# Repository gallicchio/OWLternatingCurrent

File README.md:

# OWLternating Current

*By Jason Gallicchio, made with Claude. A cute, physics-y Halloween board set for a
six-year-old witch who wants to be an owl: owls, bats and a little witch on her broom
across a gold moon, in orange and purple light that fades but never blinks, with magnets
and coils doing things that look like magic.*

| The base board's LEDs fading on the bench | The bat caught under the owl's perch, then hovering |
|:---:|:---:|
|  |  |

*The rev A boards working on the bench, November 2026 (quick phone clips; click for the MP4).*

*Rendered from the design files (KiCad and Blender, `tools/render_3d.py`).*

**Status (2026-10-09):** designed, every net routed on all six boards, KiCad's DRC clean,
reviewed by five readers before the first order ([`DESIGN_REVIEW.md`](DESIGN_REVIEW.md),
[`docs/REVIEW_2026-10-09.md`](docs/REVIEW_2026-10-09.md)), the JLCPCB release written
(`mfg/release/`). Ordered from JLCPCB; the boards arrived on 2026-11-05, and their
bring-up is [`BRINGUP.md`](BRINGUP.md).

## What it does

| feature | what you see | the physics |
|---|---|---|
| **Light show** | violet stars, orange pumpkins that flicker like candles, purple will-o'-wisps, owls whose eyes open at dusk | 49 LEDs on two LP5036 drivers, every change a fade; dusk and dawn from a light sensor |
| **Wireless familiars** | put the owl token or the cat token on its perch and its eyes light; each perch lights only its own animal | resonant inductive power: each perch drives its coil at its token's frequency (owl 142 kHz, cat 303 kHz) and finds it by the rise in its own supply current, the power the token takes |
| **The pendulum bat** | a bat on a thread that never stops swinging, or circles the moon | three coils under the swing give it timed kicks; a 3-axis Hall sensor under the rest point times them |
| **The levitating bat** | the bat floats in the air under the owl's perch | a magnet in the printed owl holds the bat's magnet up; a 10 kHz loop on a Hall sensor and the perch's coil keeps it from falling or jumping up (Earnshaw's theorem says it cannot float on magnets alone) |
| **Theremin** | move a hand toward the gold moon and a note rises; toward the gold ghost and it gets louder | two relaxation oscillators whose capacitance includes your hand; a speaker a slide switch turns off |
| **The spell book** | the back of the base: the equations behind each trick | silkscreen |

## The boards

One 4-layer panel (JLCPCB, 1.6 mm, purple solder mask, ENIG), assembled by JLCPCB on both
sides, all but three connectors (the tree's two headers and the perch's socket, soldered at
home: 48 joints). The six boards snap apart and plug together: the tree stands in the
base's socket, the perch sits on the tree.

| board | from above | from below | in perspective |
|---|---|---|---|
| **Base** (190 x 130 mm): the electronics underneath, the scene on top |  |  |  |
| **Tree** (76 x 112 mm): the owls' eyes, stars, the second LED driver |  |  |  |
| **Perch**: the levitation coil, the Hall sensor in its middle |  |  |  |
| **Bat**: a receive coil round its magnet, LED eyes, no battery |  |  |  |
| **Owl token**: a coil, a tank capacitor, two LEDs |  |  |  |
| **Cat token** |  |  |  |

The panel as it comes from JLCPCB (245.2 x 223.2 mm), top and bottom:

## Making one

- [`ORDER_LIST.md`](ORDER_LIST.md): everything to buy (the boards, three connectors, a
  12 V adapter, two magnets, a little PLA, thread and a drop of glue) and what it costs
  (about $565 for five panels, two of them assembled).
- [`mfg/release/`](mfg/release/): the upload for JLCPCB, and `FABRICATION_NOTES.txt`,
  which walks down their order form field by field.
- [`print/README.md`](print/README.md): the owl, the bat's cap and four feet, on one plate,
  with one pause to drop in the magnets.
- [`firmware/README.md`](firmware/README.md): the RP2354A's firmware, flashed over USB-C.
- [`BRINGUP.md`](BRINGUP.md): the first power-up, step by step, with the bench scripts in
  [`bringup/`](bringup/) (the supply, scope and generator from Python, and a simulated
  bench to try every step on).

## Building it from source

Everything is generated from scripts: nothing on the boards is drawn by hand in KiCad.

```
python3 build.py              # every step, about 40 minutes
python3 build.py board        # from one step on
python3 build.py --only drc   # one step
```

The steps: the KiCad library, the project and its rules, the schematics, ERC, the
netlist's checks, the art, the boards (placement, planned copper, routing, pours), DRC,
the JLCPCB release, and the pictures on this page. It needs KiCad 10, Blender 4.2 or later
and Python 3. The outputs (`hardware/`, `mfg/release/`, `docs/images/`) are committed, so
nothing has to be built to look at the design or to order it.

## What's where

| path | what |
|---|---|
| [`DESIGN_REVIEW.md`](DESIGN_REVIEW.md) | the design, subsystem by subsystem, with its numbers, its checks and its open questions |
| [`BRINGUP.md`](BRINGUP.md), [`bringup/`](bringup/) | bringing the boards up at the bench, step by step, with the scripts and each day's results |
| [`bringup/REVB.md`](bringup/REVB.md) | everything rev B should change, and every question the bench has not yet answered |
| [`hardware/`](hardware/) | the KiCad project: schematics, the panel, the library, the checks' reports |
| [`gen/`](gen/) | the generators: parts, schematics, placement, art, coils, routing, the panel |
| [`mfg/`](mfg/) | the JLCPCB release and its checks |
| [`firmware/`](firmware/) | the firmware, with host tests against simulated physics |
| [`print/`](print/) | the 3D-printed parts (OpenSCAD, from the same numbers as the boards) |
| [`sim/physics/`](sim/physics/README.md) | magnetostatics and circuit simulations: wireless power, pendulum kicks, levitation |
| [`sim/antenna/`](sim/antenna/) | an openEMS study of character-shaped 2.4 GHz antennas, for a later revision |
| [`tools/`](tools/) | checks, renders, KiCad helpers |
| [`PLAN.md`](PLAN.md) | the ideas (41, with difficulty, cost and first-try odds), the choices, the schedule |
| [`CLAUDE_CODE_CHAT.md`](CLAUDE_CODE_CHAT.md) | the conversation that designed it, every prompt and response |
| [`research/`](research/) | the JLCPCB parts survey and the web research notes |

The first concept sketch, before anything was drawn:

Licence: hardware CERN-OHL-P-2.0, software MIT ([`LICENSE`](LICENSE)).

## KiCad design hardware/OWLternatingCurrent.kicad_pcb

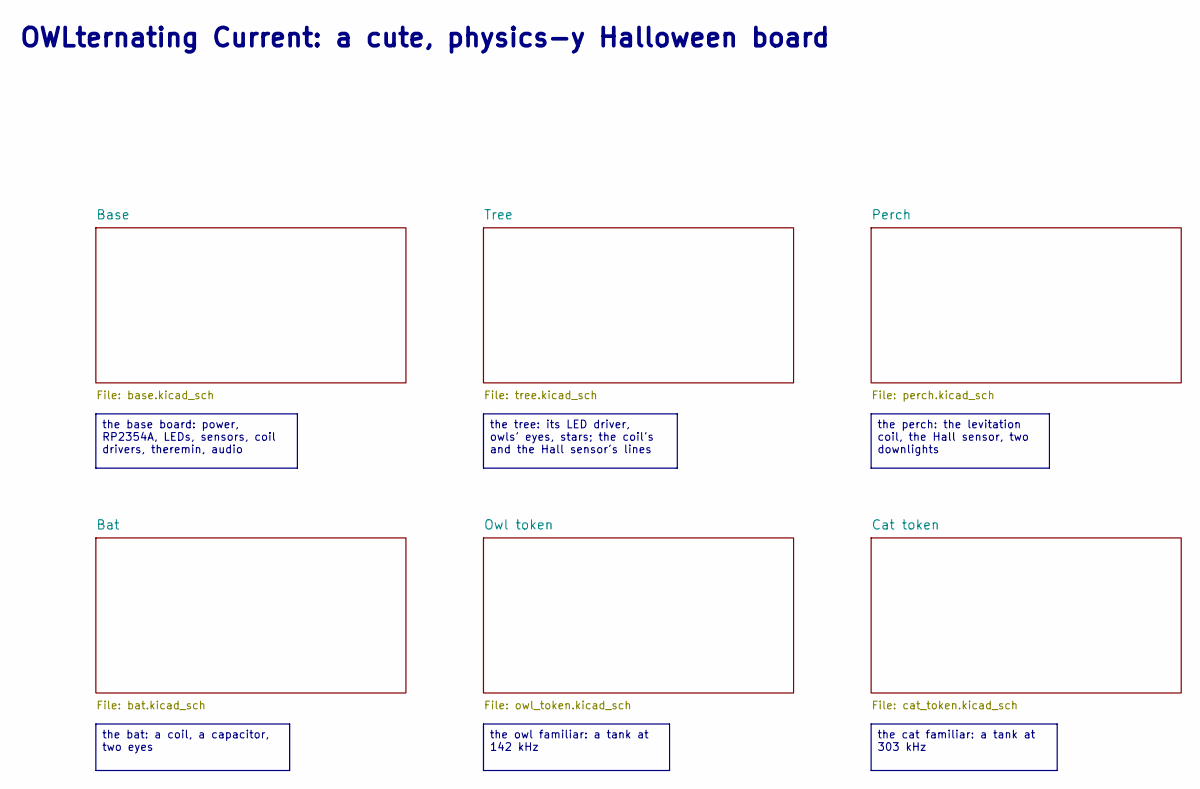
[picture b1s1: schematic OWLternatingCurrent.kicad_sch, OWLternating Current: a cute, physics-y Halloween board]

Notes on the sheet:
OWLternating Current: a cute, physics-y Halloween board
the base board: power, RP2354A, LEDs, sensors, coil drivers, theremin, audio
the owl familiar: a tank at 142 kHz
the bat: a coil, a capacitor, two eyes
the cat familiar: a tank at 303 kHz
the tree: its LED driver, owls' eyes, stars; the coil's and the Hall sensor's lines
the perch: the levitation coil, the Hall sensor, two downlights

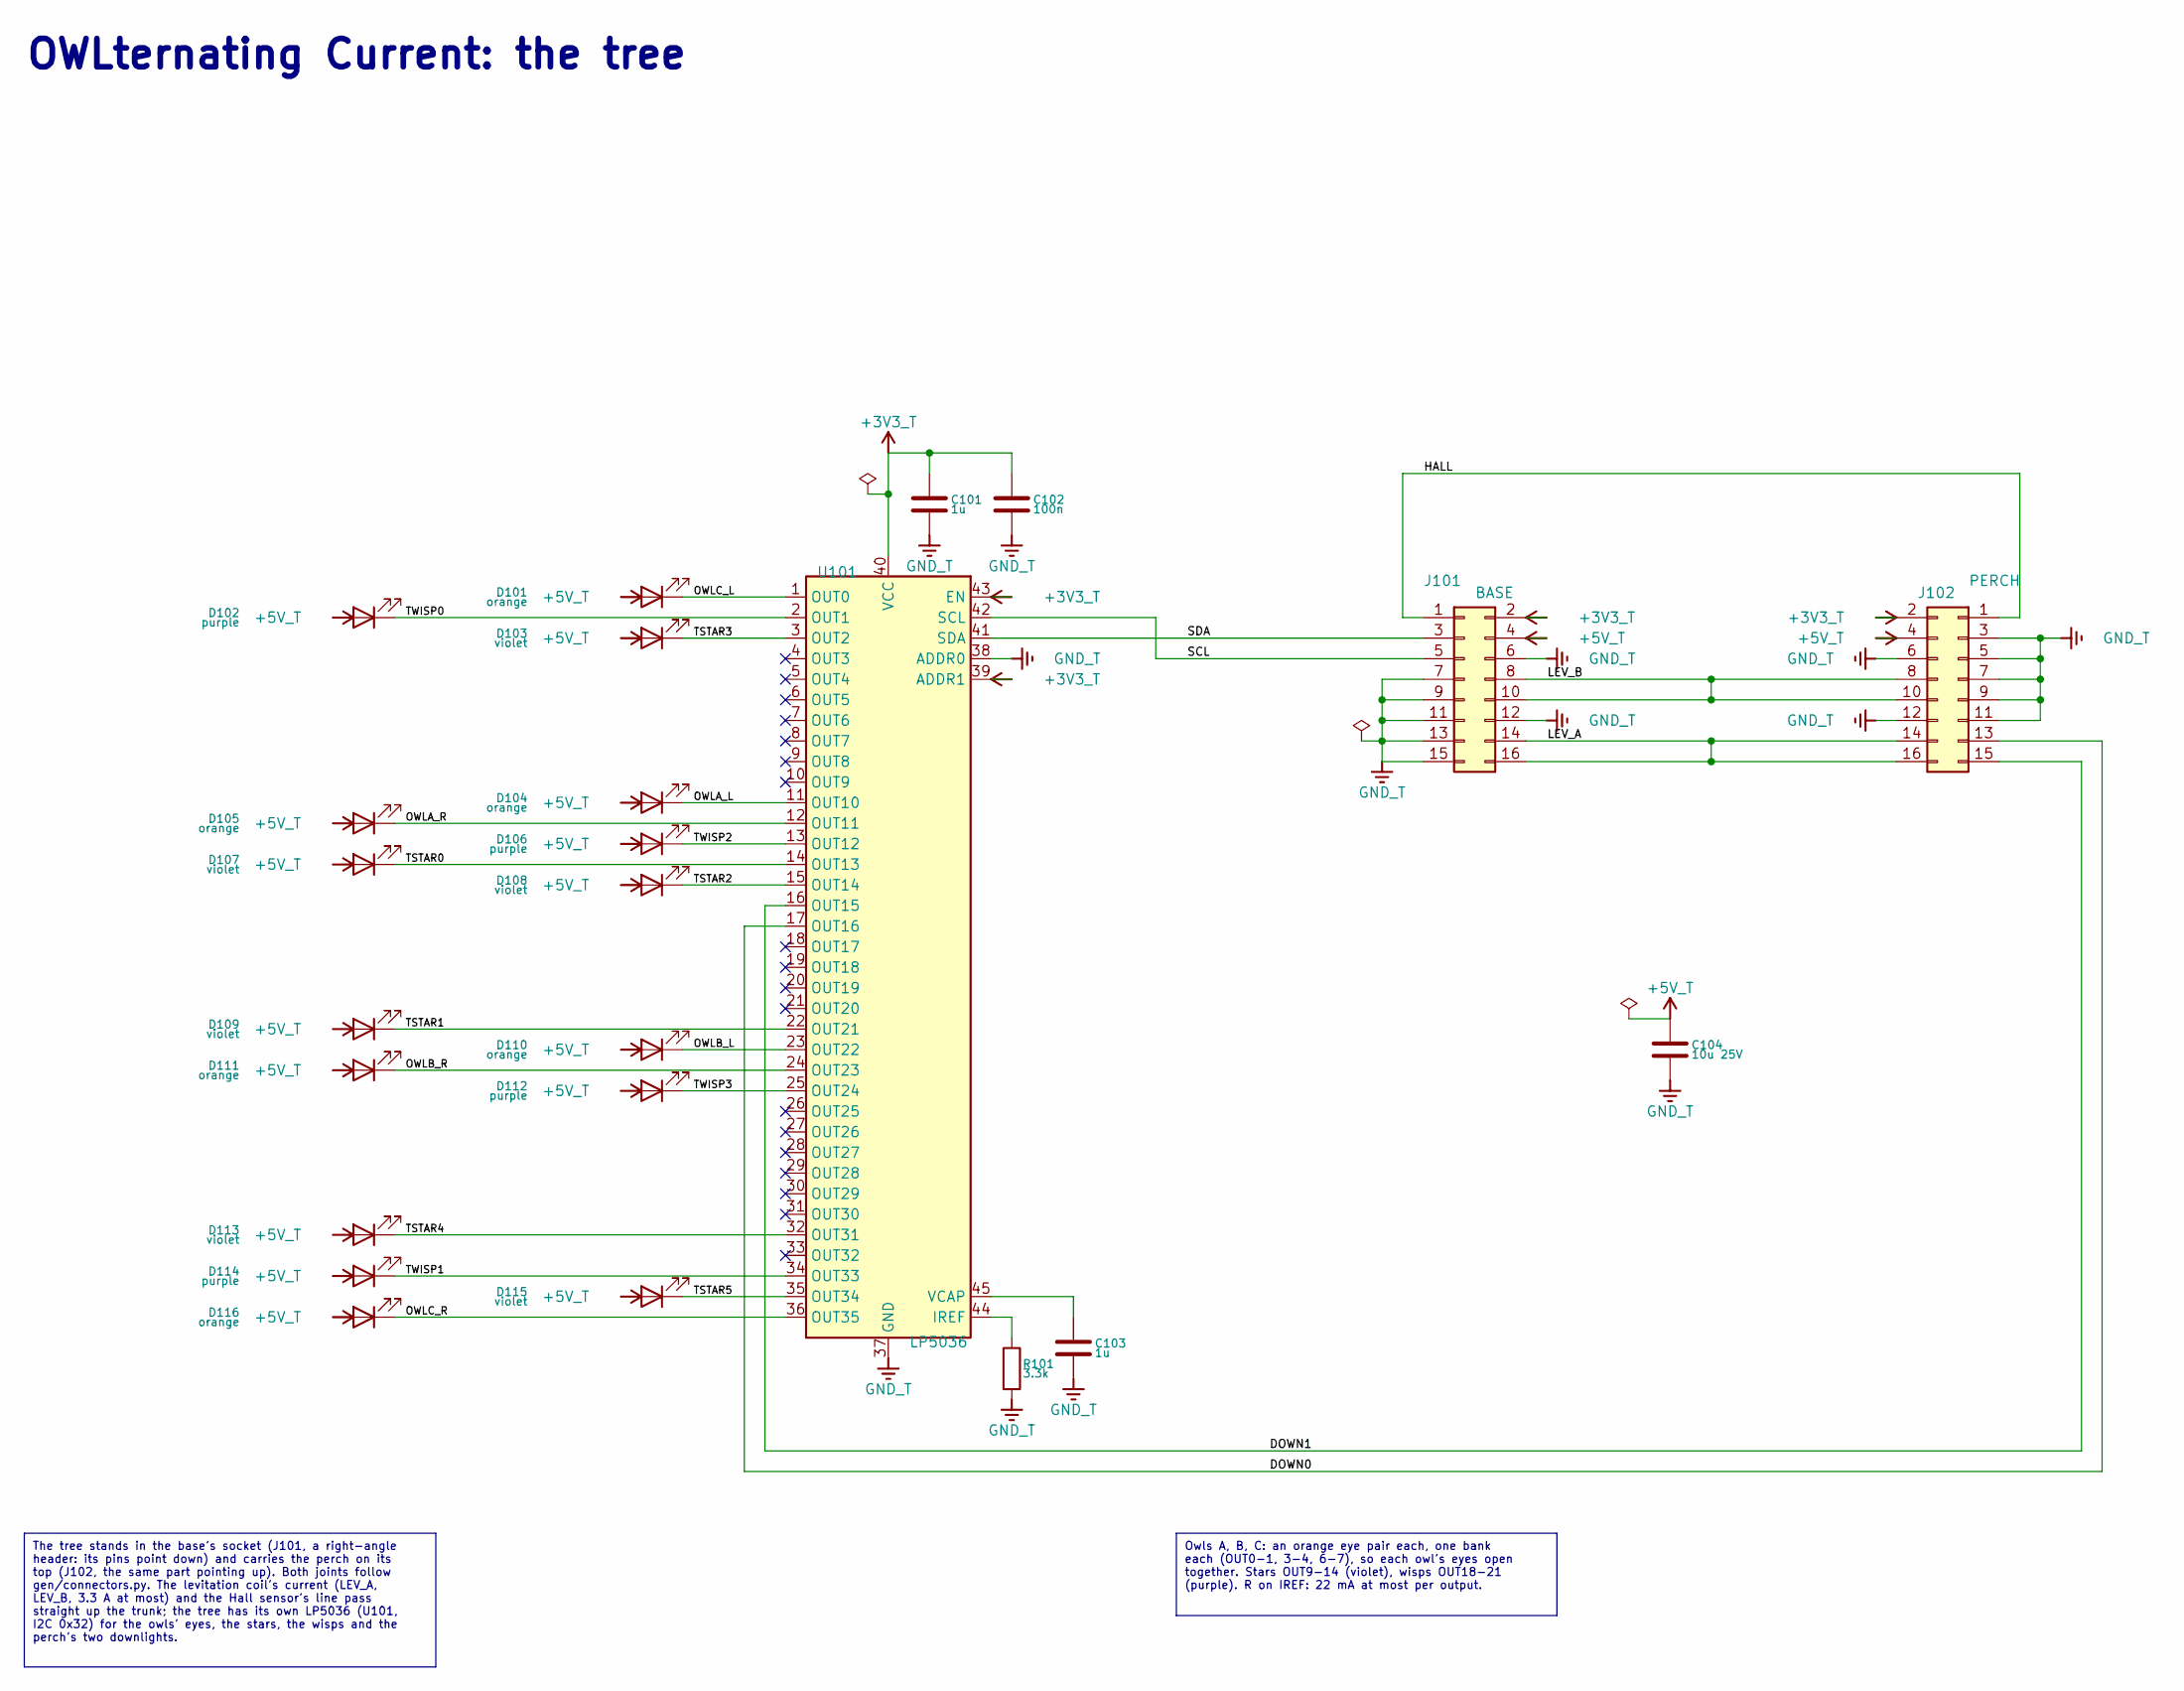
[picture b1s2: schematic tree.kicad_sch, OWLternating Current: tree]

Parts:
C101, C103: 1u; C_0603_1608Metric; MPN CL10A105KB8NNNC; LCSC C15849
C102: 100n; C_0603_1608Metric; MPN CC0603KRX7R9BB104; LCSC C14663
C104: 10u 25V; C_0805_2012Metric; MPN CL21A106KAYNNNE; LCSC C15850
D101, D104, D105, D110, D111, D116: orange; LED_0603_1608Metric; MPN XL-1608UOC-06; LCSC C965800
D102, D106, D112, D114: purple; LED_0603_1608Metric; MPN GL0603PU01; LCSC C51933300
D103, D107, D108, D109, D113, D115: violet; LED_Everlight-SMD3528_3.5x2.8mm_67-21ST; MPN HL-A-3528S7VC-S1-13HL; LCSC C516136
J101: BASE; PinHeader_2x08_P2.54mm_Horizontal; MPN PZ254-2-08-W-8.5; LCSC C2894988
J102: PERCH; PinHeader_2x08_P2.54mm_Horizontal; MPN PZ254-2-08-W-8.5; LCSC C2894988
R101: 3.3k; R_0603_1608Metric; MPN 0603WAF3301T5E; LCSC C22978
U101: LP5036; VQFN-46-1EP_5x6mm_P0.4mm_EP2.8x3.8mm; MPN LP5036RJVR; LCSC C701961

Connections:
+3V3_T: C101.1, C102.1, J101.2, J102.2, U101.39 (ADDR1), U101.40 (VCC), U101.43 (EN)
+5V_T: C104.1, D101.2 (A), D102.2 (A), D103.2 (A), D104.2 (A), D105.2 (A), D106.2 (A), D107.2 (A), D108.2 (A), D109.2 (A), D110.2 (A), D111.2 (A), D112.2 (A), D113.2 (A), D114.2 (A), D115.2 (A), D116.2 (A), J101.4, J102.4
/Tree/DOWN0: J102.13, U101.17 (OUT16)
/Tree/DOWN1: J102.15, U101.16 (OUT15)
/Tree/HALL: J101.1, J102.1
/Tree/LEV_A: J101.14, J101.16, J102.14, J102.16
/Tree/LEV_B: J101.8, J101.10, J102.8, J102.10
/Tree/OWLA_L: D104.1 (K), U101.11 (OUT10)
/Tree/OWLA_R: D105.1 (K), U101.12 (OUT11)
/Tree/OWLB_L: D110.1 (K), U101.23 (OUT22)
/Tree/OWLB_R: D111.1 (K), U101.24 (OUT23)
/Tree/OWLC_L: D101.1 (K), U101.1 (OUT0)
/Tree/OWLC_R: D116.1 (K), U101.36 (OUT35)
/Tree/SCL: J101.5, U101.42 (SCL)
/Tree/SDA: J101.3, U101.41 (SDA)
/Tree/TSTAR0: D107.1 (K), U101.14 (OUT13)
/Tree/TSTAR1: D109.1 (K), U101.22 (OUT21)
/Tree/TSTAR2: D108.1 (K), U101.15 (OUT14)
/Tree/TSTAR3: D103.1 (K), U101.3 (OUT2)
/Tree/TSTAR4: D113.1 (K), U101.32 (OUT31)
/Tree/TSTAR5: D115.1 (K), U101.35 (OUT34)
/Tree/TWISP0: D102.1 (K), U101.2 (OUT1)
/Tree/TWISP1: D114.1 (K), U101.34 (OUT33)
/Tree/TWISP2: D106.1 (K), U101.13 (OUT12)
/Tree/TWISP3: D112.1 (K), U101.25 (OUT24)
GND_T: C101.2, C102.2, C103.2, C104.2, J101.6, J101.7, J101.9, J101.11, J101.12, J101.13, J101.15, J102.3, J102.5, J102.6, J102.7, J102.9, J102.11, J102.12, R101.2, U101.37 (GND), U101.38 (ADDR0), U101.46 (GND), U101.47 (GND)
unnamed: R101.1, U101.44 (IREF)
unnamed: C103.1, U101.45 (VCAP)

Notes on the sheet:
OWLternating Current: the tree
The tree stands in the base's socket (J101, a right-angle header: its pins point down) and carries the perch on its top (J102, the same part pointing up). Both joints follow gen/connectors.py. The levitation coil's current (LEV_A, LEV_B, 3.3 A at most) and the Hall sensor's line pass straight up th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
Owls A, B, C: an orange eye pair each, one bank each (OUT0-1, 3-4, 6-7), so each owl's eyes open together. Stars OUT9-14 (violet), wisps OUT18-21 (purple). R on IREF: 22 mA at most per output.

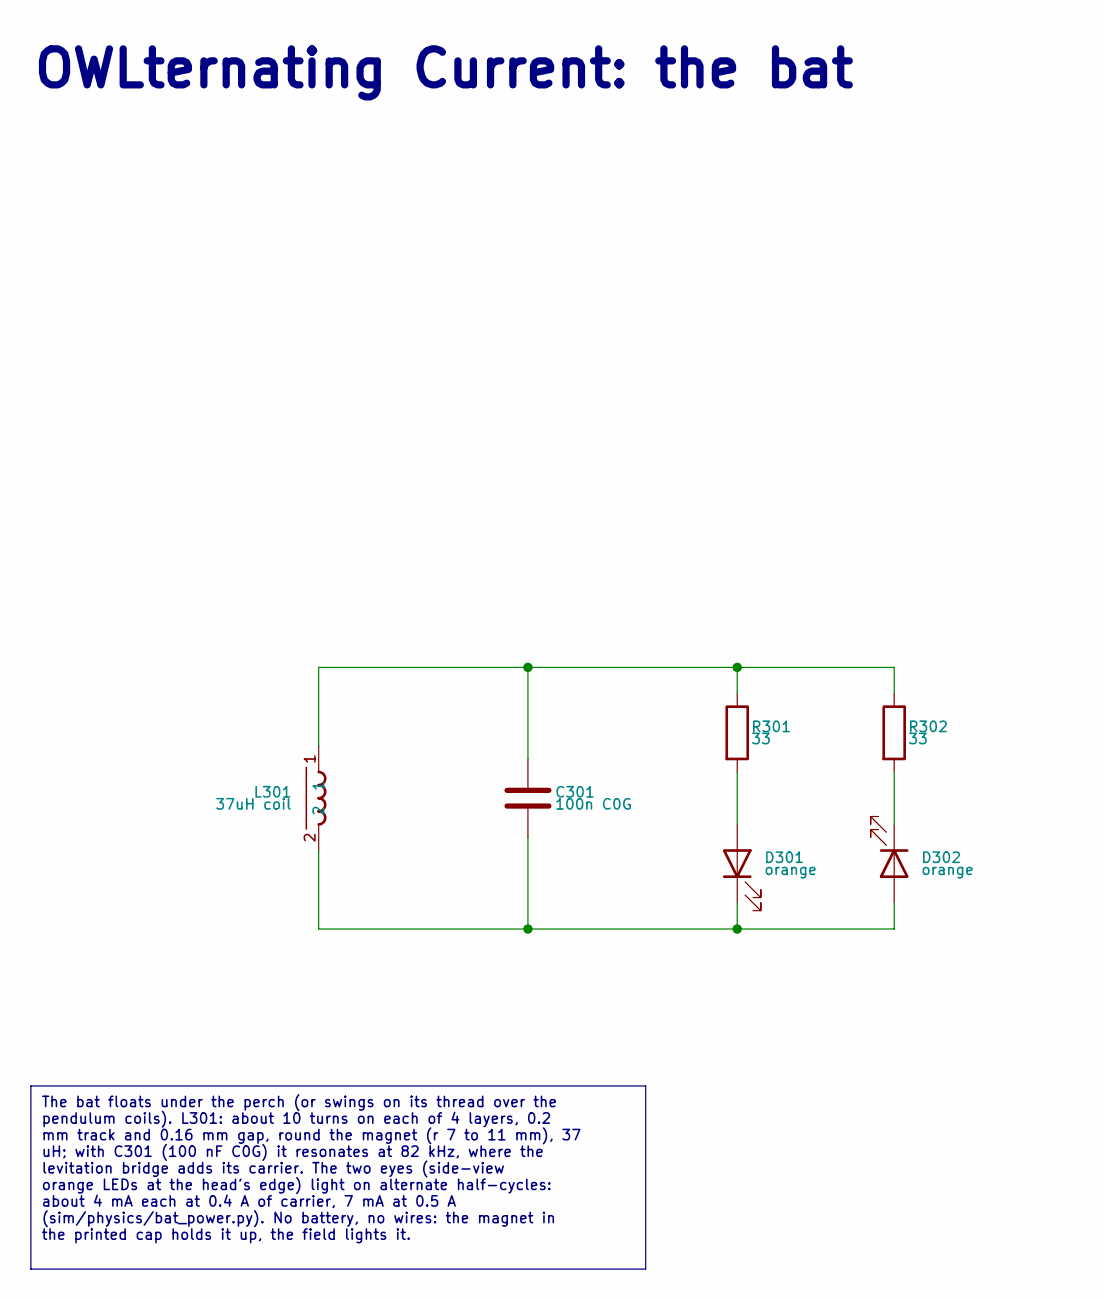
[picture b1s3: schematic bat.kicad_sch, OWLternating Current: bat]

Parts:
C301: 100n C0G; C_1206_3216Metric; MPN GRM31C5C1H104JA01L; LCSC C97946
D301, D302: orange; LED_LiteOn_LTST-S270_SideView; MPN LTST-S270KFKT; LCSC C160472
L301: 37uH coil; Coil_BAT; MPN PCB coil
R301, R302: 33; R_0603_1608Metric; MPN 0603WAF330JT5E; LCSC C23140

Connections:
unnamed: C301.1, L301.1, R301.1, R302.1
unnamed: D301.2 (A), R301.2
unnamed: C301.2, D301.1 (K), D302.2 (A), L301.2
unnamed: D302.1 (K), R302.2

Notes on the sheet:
OWLternating Current: the bat
The bat floats under the perch (or swings on its thread over the pendulum coils). L301: about 10 turns on each of 4 layers, 0.2 mm track and 0.16 mm gap, round the magnet (r 7 to 11 mm), 37 uH; with C301 (100 nF C0G) it resonates at 82 kHz, where the levitation bridge adds its carrier. The two eyes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

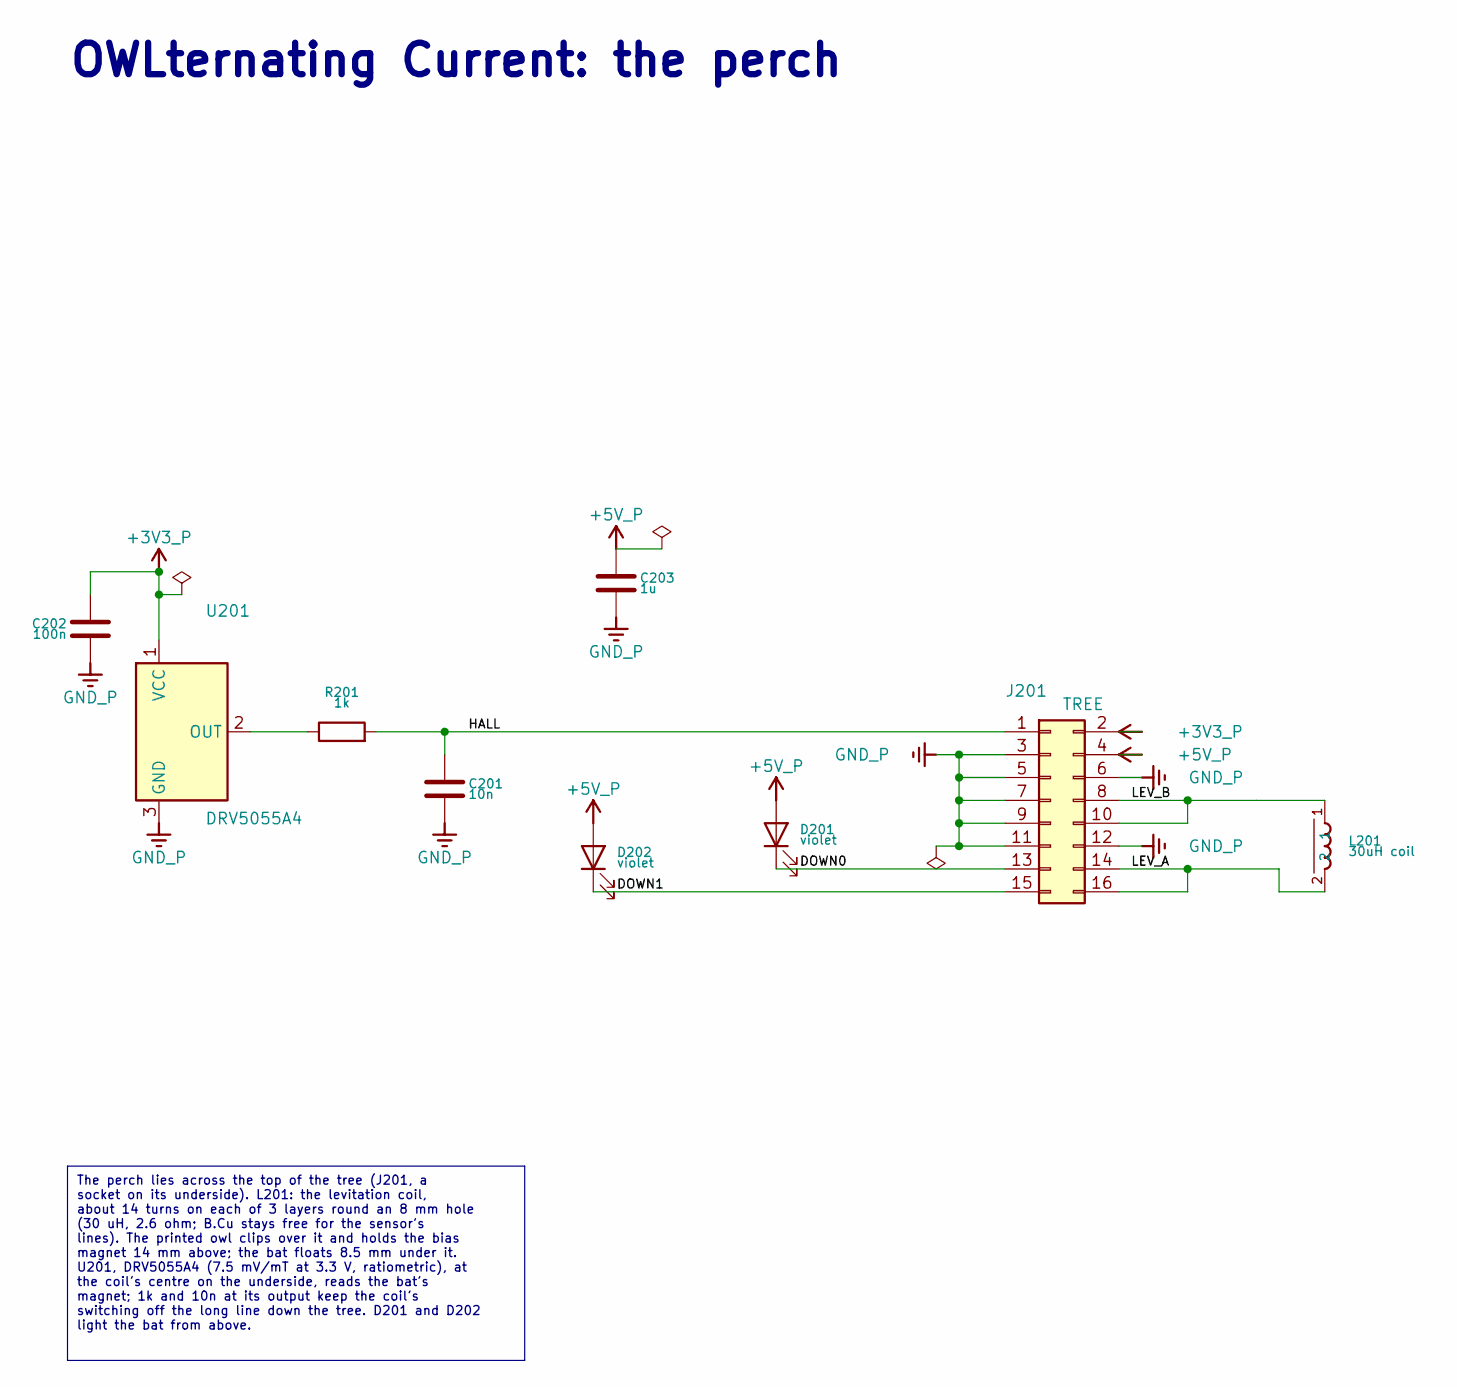
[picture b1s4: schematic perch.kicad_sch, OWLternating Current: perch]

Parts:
C201: 10n; C_0603_1608Metric; MPN 0603B103K500NT; LCSC C57112
C202: 100n; C_0603_1608Metric; MPN CC0603KRX7R9BB104; LCSC C14663
C203: 1u; C_0603_1608Metric; MPN CL10A105KB8NNNC; LCSC C15849
D201, D202: violet; LED_Everlight-SMD3528_3.5x2.8mm_67-21ST; MPN HL-A-3528S7VC-S1-13HL; LCSC C516136
J201: TREE; PinSocket_2x08_P2.54mm_Vertical; MPN PM254-2-08-Z-8.5; LCSC C2897409
L201: 30uH coil; Coil_LEV; MPN PCB coil
R201: 1k; R_0603_1608Metric; MPN 0603WAF1001T5E; LCSC C21190
U201: DRV5055A4; SOT-23; MPN DRV5055A4QDBZR; LCSC C266123

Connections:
+3V3_P: C202.1, J201.2, U201.1 (VCC)
+5V_P: C203.1, D201.2 (A), D202.2 (A), J201.4
/Perch/DOWN0: D201.1 (K), J201.13
/Perch/DOWN1: D202.1 (K), J201.15
/Perch/HALL: C201.1, J201.1, R201.2
/Perch/LEV_A: J201.14, J201.16, L201.2
/Perch/LEV_B: J201.8, J201.10, L201.1
GND_P: C201.2, C202.2, C203.2, J201.3, J201.5, J201.6, J201.7, J201.9, J201.11, J201.12, U201.3 (GND)
unnamed: R201.1, U201.2 (OUT)

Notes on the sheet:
OWLternating Current: the perch
The perch lies across the top of the tree (J201, a socket on its underside). L201: the levitation coil, about 14 turns on each of 3 layers round an 8 mm hole (30 uH, 2.6 ohm; B.Cu stays free for the sensor's lines). The printed owl clips over it and holds the bias magnet 14 mm above; the bat floats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

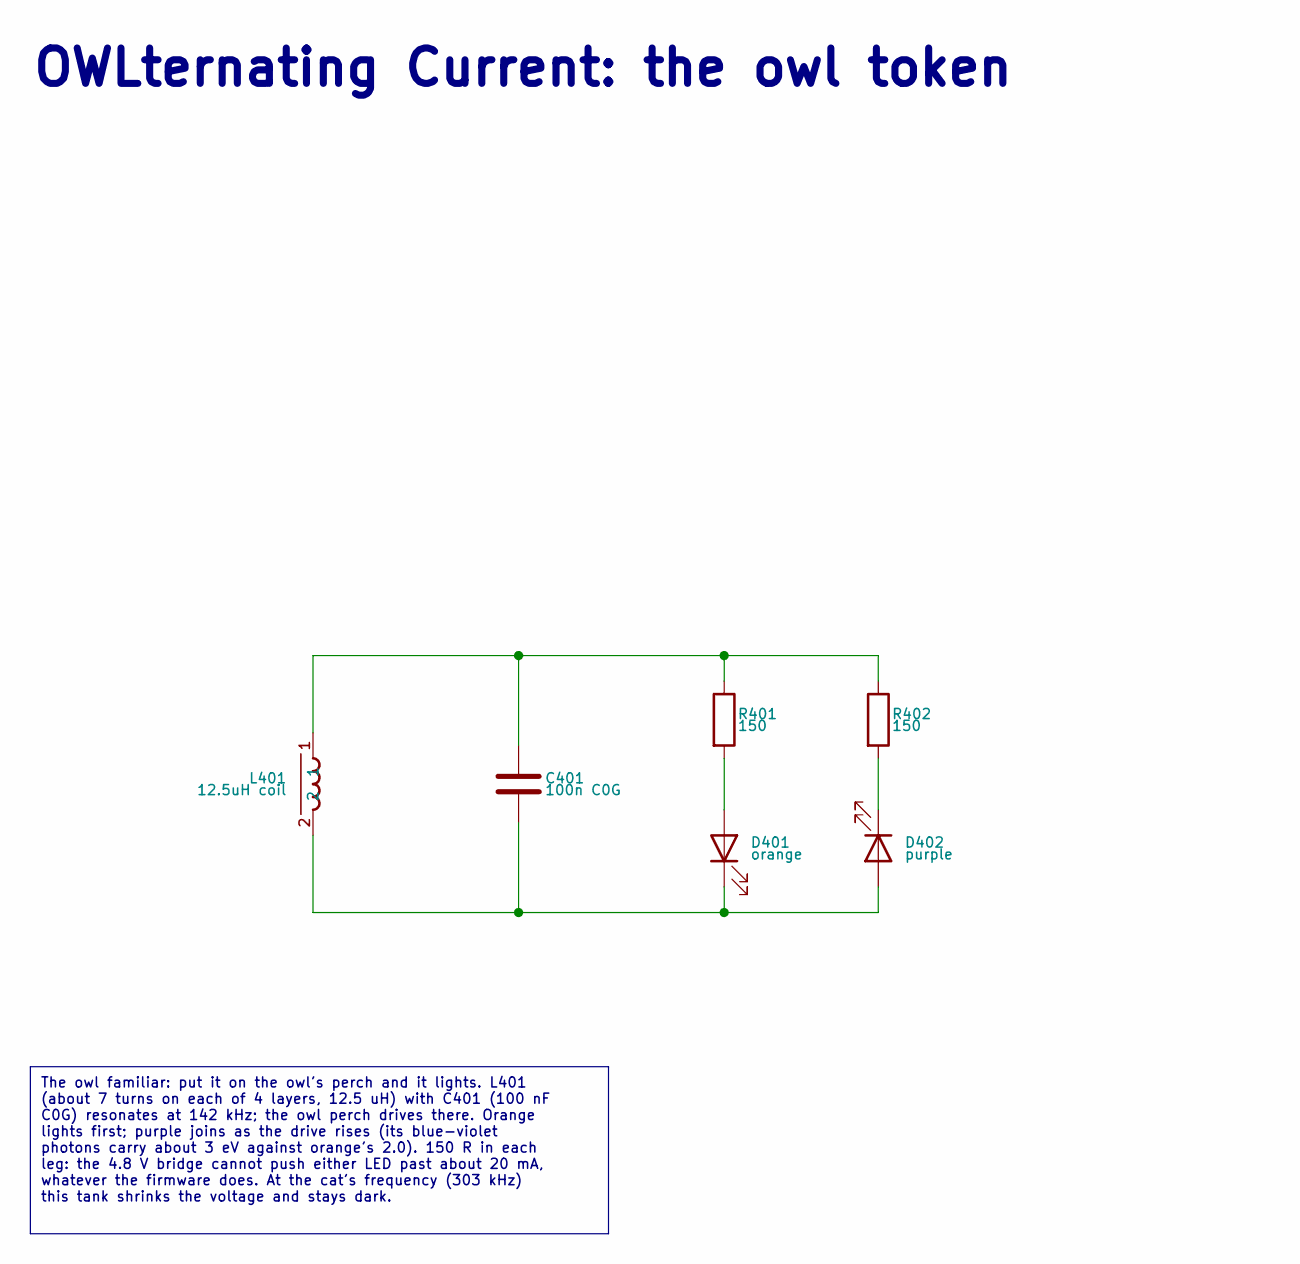
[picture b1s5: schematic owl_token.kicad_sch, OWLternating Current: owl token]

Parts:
C401: 100n C0G; C_1206_3216Metric; MPN GRM31C5C1H104JA01L; LCSC C97946
D401: orange; LED_0603_1608Metric; MPN XL-1608UOC-06; LCSC C965800
D402: purple; LED_0603_1608Metric; MPN GL0603PU01; LCSC C51933300
L401: 12.5uH coil; Coil_TOKEN; MPN PCB coil
R401, R402: 150; R_0603_1608Metric; MPN 0603WAF1500T5E; LCSC C22808

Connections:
unnamed: C401.1, L401.1, R401.1, R402.1
unnamed: D401.2 (A), R401.2
unnamed: C401.2, D401.1 (K), D402.2 (A), L401.2
unnamed: D402.1 (K), R402.2

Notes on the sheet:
OWLternating Current: the owl token
The owl familiar: put it on the owl's perch and it lights. L401 (about 7 turns on each of 4 layers, 12.5 uH) with C401 (100 nF C0G) resonates at 142 kHz; the owl perch drives there. Orange lights first; purple joins as the drive rises (its blue-violet photons carry about 3 eV against orange's 2.0).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

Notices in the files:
parts and their libraries:
From Raspberry Pi's RP2350A Minimal design (MIT licence), so their regulator layout can be copied exactly
